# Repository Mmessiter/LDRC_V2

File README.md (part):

# LockDownRadioControl, Version 2

**A free, open-source radio control system for model aircraft. You build it yourself: a 16-channel transmitter, a receiver and a phone app.**

**Nothing to compile.** Every part takes ready-made firmware: the screen and the receiver from a web browser, the main board with a free loader. After that, everything updates itself over the air. [The short route is below](#how-to-get-one).

<p align="center"><sub>Nine of the transmitter's screens, drawn by its own code. The numbers are sample values.</sub></p>

| I want to… | Go here |
|---|---|
| See what LDRC does | [messiter.com/LDRC.html](https://messiter.com/LDRC.html) |
| Build one | [Build one](https://messiter.com/ldrc/build.html): parts, wiring, flashing, testing. [The short route](#how-to-get-one) is on this page |
| Update, or get help | [Help & updates](https://messiter.com/ldrc/help.html) |
| Set up Rotorflight from my phone | [messiter.com/rotorflight](https://messiter.com/rotorflight/) |
| Ask a question | Email Malcolm: [mmessiter@gmail.com](mailto:mmessiter@gmail.com) |

---

## What LDRC is

- **Malcolm Messiter started it in the lockdown of May 2020.** He and his club friends have flown it ever since.
- **Version 1** is in the [LockDownRadioControl](https://github.com/Mmessiter/LockDownRadioControl) repository. It still flies.
- **This repository is Version 2.** It keeps Version 1's radio link and model memories, and adds:
  - a 5-inch WiFi touchscreen on the transmitter,
  - a new receiver,
  - a free phone app for iPhone, iPad and Android.
- It flies planes, gliders and helicopters.
- It is at its best with helicopters that run [Rotorflight](https://www.rotorflight.org/), the free flight-controller software for helicopters.

## The three parts

### 1. The transmitter

<sub>A finished Version 2 transmitter (Malcolm's). The screen shows its front page.</sub>
<!-- (11 Nov 2026: Malcolm's photo of the whole white Version 2, screen lit, replaces the dim black one - his answer to question 42. One in daylight beside a helicopter is still welcome.) -->

- **The main board flies the model.** A Teensy 4.1 reads the sticks, does the mixing and runs the radio link.
- **The screen talks to the pilot.** An Elecrow 5-inch ESP32-S3 touchscreen (buy the **16 MB** one, SKU DLE06050B: the older 4 MB CrowPanel 5.0 gets fixes only) draws the pages and looks after WiFi, Bluetooth and updates.
- FrSky M9 Hall-sensor sticks, digital trims, eight three-position switches (four can be knobs), a 3D-printed case.
- **A Version 1 transmitter becomes a Version 2.** Your models, main board, sticks, switches and case back stay (fill the back's old charger hole with epoxy resin). Print the Version 2 case front from [TXV2/STL files/V2](TXV2/STL%20files/V2): it holds the new screen. Fit the screen, and update the firmware.
  <!-- (10 Nov 2026, Malcolm: "A version one back is okay, except it has an unnecessary hole for the old style charger, but it can be used if this hole is blocked up with epoxy resin".) -->
- Details: [TXV2/README.md](TXV2/README.md) and [TXV2-Screen/README.md](TXV2-Screen/README.md).

### 2. The receiver

<sub>A Version 2 receiver in a Goblin 770, beside its Nexus-X flight controller. With the short USB-C cable, the phone app does almost everything Rotorflight's Configurator does. Only flashing Rotorflight itself needs a computer.</sub>

- **A Seeed XIAO ESP32-S3 with one, two or three nRF24L01+ radios.** If one radio loses the signal, the next takes over.
- **Talks to a flight controller** over CRSF, SBUS, IBUS or PPM.
- **Sends Rotorflight telemetry** to the transmitter: battery, current, capacity used, head speed, ESC temperature.
- **Updates itself over the air**: from the phone, over WiFi, or through a Version 2 transmitter.
- **Binds to Version 1 and Version 2 transmitters.**
- **The same board has two other jobs:**
  - **dongle**: Rotorflight from your phone on a helicopter flown with any make of radio;
  - **simulator**: plugged into a computer, it lets your transmitter fly RealFlight or neXt (with no radios, it does the same for another make of receiver).
- Details: [RXV2/README.md](RXV2/README.md).

### 3. The phone app

<sub>The app's demo mode. It works without any hardware, so you can look round before you build.</sub>

- **Free** on the [App Store](https://apps.apple.com/app/id6789857533) (iPhone and iPad) and for Android from [messiter.com/apps](https://messiter.com/apps/). No adverts, no accounts, no tracking.
- **Talks to the receiver over Bluetooth.** No WiFi to join at the field.
- **Sets up Rotorflight in plain English**: wizards for a new helicopter and for tuning, PIDs, rates, governor, rescue, servos, filters, backups.
- **Reads the flight controller's black box** and suggests one filter change at a time.
- Source in [RXV2App](RXV2App).

---

## Why fly LDRC

**What gets used, and what does not.** Compare feature lists and every radio has something the others lack. What matters is which features a pilot reaches for. The ones LDRC has that most systems do not are wanted at the field all the time: a model that loads itself when you switch it on, a model or the controls handed to a friend over the air with nothing extra to buy, the whole radio updated from a button, Rotorflight set up from the transmitter. The few things other radios have that LDRC does not are rarely used by anyone, and since every line of LDRC is open they can be added the day a pilot asks: the 3-, 7- and 9-point curves were asked for one October morning and were in the transmitter by lunch.

**Range and channels: more than enough.** Some radios offer more range and more channels. Sixteen channels and about 2 km of range are more than enough for almost all model flying. [Here is why](#range-and-channels-more-than-enough).

**Every save is checked.** After a save, the transmitter and the phone app read the values back from the flight controller and compare them with what you typed. "Saved, and confirmed by reading it back" means the flight controller now holds exactly your values; a difference, or no answer, is said plainly, with the boxes that differ in red. Neither ever says "saved" on trust. Just before every write, the transmitter asks the flight controller whether it is armed; if an answer goes missing, the save is refused, never guessed. And the receiver refuses a tune that would leave roll, pitch or yaw with no response.

### Things we know of no other system doing

We checked the makers' own documents in October 2026, and read Rotorflight's three script projects for other radios again on 10 November 2026. "We know of no other" means we did not find it, not that it cannot exist.

1. **The Rotorflight tune and set-up, every bank, backed up on the transmitter and put back exactly.** Each write is read back to check it. After a restore, Rotorflight's own list of changed settings (its `diff all`) was identical to before. Ports, LED, GPS and ESC settings are not included. *Copy tuning* writes another model's PIDs, rates, governor and rescue from its backup into this one; servos, mixer, motor and switches are left alone.
2. **Change Rotorflight settings with the model switched off.** The changes are sent when the model next connects.
3. **The whole Rotorflight set-up compared with its backup, on the transmitter** (*What changed?*, 16 MB screen). Setting by setting. *Put back* returns one setting; *Undo the last save* takes back a save.
4. **Rotorflight's command line on the transmitter's screen**, and the whole set-up saved as text. (This needs the receiver's short USB cable to the flight controller.)
5. **Rotorflight set-up from an iPhone or iPad**, in plain English, with step-by-step wizards. Android too.
6. **For Rotorflight: read the black box at the field, with no computer.** See the vibration and get one filter change at a time, with undo.
7. **A chart of how long the link took to reconnect** after every drop.

<p align="center"><sub>What changed? since the backup, setting by setting. Put back returns one setting. Sample values.</sub></p>

**Rare: the right model memory loads by itself.** Switch on a model and the transmitter finds its memory. Most radios only stop you flying with the wrong one. Elsewhere we found this only on Multiplex's SMART SX, with its ID receivers (some have a fixed ID, some can be set), and on Mikado's VBar Control, which does it another way: each model's settings live in its VBar unit. Ours learns the ID of any of its own receivers.
<!-- Source: Multiplex shop, RX-5 M-LINK ID receiver: "SMART SX automatically changes the respective model memory based on the ID of the receiver" (shop.multiplex-rc.de, checked 11 Oct 2026). SMART SX 9 FLEXX M-LINK set: the RX-4/9 FLEXX M-LINK ID receiver has an adjustable ID (hobbydirekt.de/Alte-Kategorien/RC/Multiplex-RC/SMART-SX-9-FLEXX-M-LINK-Set-Multiplex-15303::270611.html, checked 11 Oct 2026). -->

<!-- TODO Malcolm: compare.md notes the Battery, Black box and Calibrate pages on the transmitter (B88) had not been tried on hardware on 10 Oct. Confirm before the site calls them proven. -->

<p align="center"><sub>Rotorflight set-up on the transmitter itself. It needs a Version 2 receiver.</sub></p>

**A new helicopter, step by step, on the transmitter** (16 MB screen). You need no laptop and no phone at the field.

- **New helicopter guide**: every Rotorflight set-up step in order. A step opens its page, and is ticked when you come back. The ticks are kept for each model.
- **Check my setup**: reads the flight controller and lists anything unfinished or odd, with a button to the page that puts it right. Red stops the model arming; amber is worth a look. It changes nothing.
- **Direction check**: tilt and turn the model, and it says whether the flight controller sees each move the right way round.
- Only putting Rotorflight itself onto the flight controller needs a computer.

<p align="center"><sub>Left: the New helicopter guide ticks off each step. Right: Check my setup says what stops the model arming. Sample values.</sub></p>

### Also on board

Other systems have most of these too.

- **Wireless buddy box** with no extra modules, and a "nudge" mode: the pupil flies, the instructor can nudge. Once it has the model, the pupil's transmitter loads it by itself. (Spektrum's Pilot Link avoids the need another way: the pupil's radio needs no model at all.)
- **Send a model memory to a friend's transmitter** over the radio link. A Version 1 transmitter can send its models to a Version 2 over the air (tested), and two Version 2s swap them.
- **One-button updates from the internet** for the whole transmitter. It can update the receiver too, and it tells you when a new version is ready.
- **Updates that protect your models**: a firmware that would read your models differently is refused, and the old one comes back by itself.
- **The link in detail**: packets a second, lost packets, longest gap, swaps between the receiver's radios, and a scan of the 2.4 GHz band for interference.
- **Six front screens, ready-made and yours to change**: an overview, head speed, the timer, the link, power, and the model with its channels. One to nine boxes each, in big digits or round dials with amber and red zones, and twelve colour themes.
- **Four banks or six** (flight modes), as Rotorflight has six. The phone app follows the transmitter's count.
- **Curves of 3, 5, 7 or 9 points** for every channel in every bank, straight, smoothed or exponential; every point keeps its height when you change the count. **Eight three-position switches**, any of them doing any job; the four on the front can be knobs.
- **Help on every page**, on the transmitter itself: 72 help pages in plain words. Most have an **animation**: a short film of the page in use, with a spoken voice. There are 76 animations; ten of them, under **Fix problems**, cure common helicopter problems.
- **See what moves what**: the Inputs and outputs page and the Switches page light the stick, trim or switch you move. *Check for duplicates* finds a model ID stored twice.
- **Spoken messages**, log files, model pictures sent from your phone, and Pong for rainy days.
- **Safety first: nothing changes in flight.** No transmitter update, file transfer or restart starts while a model is connected. A receiver update runs only with the safety on, and the receiver refuses while armed. WiFi and Bluetooth switch off whenever the model could fly. Switch a Rotorflight model on with the safety already off, and the transmitter will not connect to it until the safety is on.

<p align="center"><sub>The six ready-made front screens. Use them as they are, or change any box. Sample values.</sub></p>

<p align="center"><sub>Left: how long the link took to come back after each drop. Right: a scan of the 2.4 GHz band. Sample values.</sub></p>

### Yours to change

LDRC changes when a need appears. Its author, Malcolm Messiter, often adds a feature within a day of a pilot asking for it: the transmitter's command line and the defined front screens were each built the day they were asked for. The new version then reaches every transmitter and receiver over the internet.

It is yours to change too. Every line of code, the circuit boards and the case are open, so you can change anything yourself, or ask for it.

Commercial systems are almost always take it or leave it: you fly what the maker decided, and you cannot easily change it.

### Range and channels: more than enough

**Some radios offer more range and more channels. Sixteen channels and about 2 km of range are more than enough for almost all model flying.**

ExpressLRS is rightly praised for its range, and its claims are fair. But with a model helicopter, the radio is not what limits range. Your eyesight is.

In Malcolm's own tests at ground level, LDRC Version 2 kept its link at more than a kilometre. The makers of its radio modules claim more than two. Nobody can see a helicopter well enough to fly it at a kilometre, so more range than that makes no difference in the air.

Channels are the same story. A helicopter with a flight controller uses about eight, and most aeroplanes fewer. Sixteen leaves room to spare.

What matters more is that the link never fails. Now and then a commercial radio fails and a model crashes, through a faulty part or faulty assembly. Commercial makers must make a profit, so they have every reason to build quickly and with economical parts. LDRC is not built for profit. In about six years of flying, it has never had a radio failure, nor any problem with range.

### Side by side

Key: **Yes** · **Partly** · **No** · **Not found** = not in the maker's documents we read · **?** = not checked, or we could not confirm · **n/a** = does not apply.
Prices are approximate retail prices in October 2026. LDRC prices are for parts only.

**Link and hardware**

| | LDRC V2 | EdgeTX + ExpressLRS | FrSky Ethos | Spektrum | Mikado VBar Control |
|---|---|---|---|---|---|
| Open-source firmware | **Yes** | **Yes** | No | No | No |
| Boards and case you can build yourself | **Yes** | Partly: ExpressLRS publishes DIY receiver and module boards; the radio is bought | No | No | No |
| Channels | 16 (a helicopter with a flight controller uses about eight) | Up to 32 (ExpressLRS carries 16) | Up to 24 | 20 | ? |
| Fastest packet rate | 500 a second | Up to 1,000 a second | ? | ? | ? |
| Bands | 2.4 GHz | 2.4 GHz and 900 MHz | 2.4 GHz and 900 MHz | 2.4 GHz | 2.4 GHz |
| Range | More than 1 km in ground-level tests (the module makers claim more than 2 km): more than enough for almost all model flying | "Over 40 km" (ExpressLRS's own figure, ideal conditions) | "50–100 km" (FrSky's claim) | ? | ? |
| Servo (PWM) outputs on the receiver | Version 1 receiver only | **Yes** | **Yes** | **Yes** | The VBar unit drives the servos |
| GPS and vario | Version 1 receiver only | **Yes** | **Yes** | **Yes** | Partly |
| CE-marked radio modules | **Yes** (Ebyte E01, FCC ID 2ALPH-E01) | **Yes** | **Yes** | **Yes** | **Yes** |
| Price, about | Transmitter: the parts priced so far come to £120–£143, before the switches, trims, radio module, battery, circuit board, case and small parts. Receiver about £35. Parts only, approximate | Radio about £130–£200 (Jumper T15 to TX16S MKII); ExpressLRS receivers from about £11 to £19 (HappyModel EP2, RadioMaster RP1), ready to fly | £460–£600 (X20 family) | £430 (NX10+) | £750 (radio + VBar EVO flybarless unit and receiver) |

**The transmitter**

| | LDRC V2 | EdgeTX + ExpressLRS | FrSky Ethos | Spektrum | Mikado VBar Control |
|---|---|---|---|---|---|
| Loads the right model memory by itself | **Yes**, rare (elsewhere found only on Multiplex SMART SX and VBar Control) | No: Model Match only blocks control | Not found | No: ModelMatch only blocks the wrong memory | **Yes**, another way: each model's settings live in its VBar unit |
| Wireless buddy box, no extra hardware | **Yes**, with nudge; the pupil's radio loads the same model | Partly: radios with Bluetooth | **Yes** | **Yes** | **Yes** |
| Send a model memory to another transmitter, no wires | **Yes**, over the radio link | No | ? | **Yes** (iX20, Bluetooth) | Partly |
| Updates itself from the internet | **Yes**, the whole radio, with automatic roll-back | No: a computer and a browser | No: USB or SD card | **Yes**, WiFi | **Yes**, WiFi |
| Updates the receiver through the transmitter | **Yes** | Partly: the receiver's own WiFi page | **Yes** | ? | **Yes** |
| Help on every page, on the radio | **Yes**: 72 help pages and 76 spoken animations | Not found: online manual | ? | ? | **Yes**: a (?) on every setting |
| Scripts and add-on apps | No, by choice | **Yes**: Lua | **Yes**: Lua | **Yes**: apps on iX20 | **Yes**: app store |
| Mixer depth | 16 channels, 4 or 6 flight modes, 32 mixes | Much deeper | Deep | Deep | Made for helicopters |
| Curve points per channel | 3, 5, 7 or 9, every point remembered | Up to 17 | ? | ? | ? |
| Any switch, any job | **Yes**: 8 three-position switches, the front four can be knobs | **Yes** | **Yes** | **Yes** | **Yes** |

**Helicopters with Rotorflight**

| | LDRC V2 | EdgeTX + ExpressLRS | FrSky Ethos | Spektrum | Mikado VBar Control |
|---|---|---|---|---|---|
| Rotorflight telemetry on the transmitter | **Yes** | **Yes** | **Yes** | Partly | **Yes**, for VBar units |
| Rotorflight set-up from the transmitter | **Yes**: Easy tuning, PIDs, rates, governor, rescue, servos, travel extents, filters, switches and knobs, copy a bank, battery, black box, first-time basics. On the 16 MB screen: a new-helicopter guide, a set-up check and a direction check | **Yes**: PIDs, rates, governor, rescue, servos, mixer, filters, battery, ESCs of 8 makes (Rotorflight's Lua scripts). A newer suite, in pre-release snapshots, adds a set-up wizard | **Yes, and wider**: over 100 pages, a set-up wizard, ESC tools | Not found | **Yes**, for VBar units |
| Back up Rotorflight on the transmitter, restore exactly | **Yes**: every bank; not ports, LED, GPS or ESC | Not in the Rotorflight scripts | No | n/a | A separate app, for VBar |
| Edit with the model switched off, send later | **Yes** | Not found | Not found | n/a | Not found |
| Compare Rotorflight with its backup, put one setting back, undo a save | **Yes** (16 MB screen) | Not found. Rotorflight's newer suite, in a preview, tracks what an in-flight tuning session changed, and can put it back | Not found | n/a | n/a |
| Phone app for Rotorflight on iPhone and Android | **Yes**, free | Partly: Rotorflight's configurator on Android (app, or Chrome at cfg.rotorflight.org), by USB cable; no iPhone app | as EdgeTX | n/a (an app for its own flybarless units) | n/a (set-up is on the radio) |
| Black box vibration check without a computer | **Yes** | No | Partly: no spectrum | No | **Yes**, for VBar |
| ESC programming | Partly: from the phone, Scorpion only, beta | **Yes**: 8 makes (Rotorflight's Lua scripts) | **Yes**: 10 ESC families | Spektrum Smart ESCs | **Yes** |

<details>
<summary>Sources for the table</summary>

- ExpressLRS: [home page](https://www.expresslrs.org/), [signal health and range](https://www.expresslrs.org/info/signal-health/), [Model Match](https://www.expresslrs.org/software/model-config-match/), [WiFi updating](https://www.expresslrs.org/software/updating/wifi-updating/), [DIY receivers](https://www.expresslrs.org/hardware/special-targets/diy-rx/)
- EdgeTX: [limits in the source](https://github.com/EdgeTX/edgetx/blob/main/radio/src/dataconstants.h), [Bluetooth](https://manual.edgetx.org/v2.9/edgetx-how-to/use-bluetooth-with-edgetx), [updating with EdgeTX Buddy](https://manual.edgetx.org/installing-and-updating-edgetx/update-from-opentx-to-edgetx)
- Rotorflight: [Lua scripts](https://github.com/rotorflight/rotorflight-lua-scripts) ([their pages in release 2.3.0](https://github.com/rotorflight/rotorflight-lua-scripts/tree/release/2.3.0/src/SCRIPTS/RF2/PAGES)), [Ethos suite](https://github.com/rotorflight/rotorflight-lua-ethos-suite), [newer suite for EdgeTX](https://github.com/rotorflight/rotorflight-lua-edgetx-suite) (snapshot 0.2.1; all three read again on 10 November 2026), [configurator releases](https://github.com/rotorflight/rotorflight-configurator/releases)
- FrSky: [Tandem X20 review](https://oscarliang.com/frsky-tandem-x20), [ACCESS receivers](https://oscarliang.com/frsky-access-protocol/)
- Spektrum: [NX10+](https://modelhelicopters.co.uk/products/spektrum-nx10-20-channel-dsmx-transmitter-only-spmr10120eu), [iX20](https://modelhelicopters.co.uk/products/spektrum-ix20-20-channel-smart-transmitter-spmr20100eu-spmr20100eu), [wireless trainer](https://cdn.shopify.com/s/files/1/0024/8617/3749/files/SPMR6775-Manual-EN.pdf) (the NX6 manual, page 22)
- Mikado: [VBar Control Touch EVO](https://modelhelicopters.co.uk/products/mikado-vcontrol-touch-evo-combo-red-05585), [release notes, Nov 2025](https://www.vstabi.info/en/update_release_nov_2025), [VBar Control Touch manual](https://www.mikado-heli.de/downloads/anleitungen/vcontrol/VBar_Control_Touch_201_EN.pdf) (help on the radio; the model's screen on connection), [Model Aviation review, August 2019](https://www.modelaviation.com/mikado-vbar-control) (each model's settings live in its VBar unit)
- Multiplex: [RX-5 M-LINK ID1 receiver](https://shop.multiplex-rc.de/en/receiver-rx-5-m-link-id-1-2-4-ghz-p5007/) (SMART SX loads the model memory from the receiver's ID)
- LDRC's own facts come from the code and help texts in this repository.

</details>

### The price, honestly

- The transmitter parts priced so far come to £120–£143, before the switches, trims, radio module, battery, circuit board, case and small parts. A budget EdgeTX radio is about £130.
- It costs far less than the X20, NX10+ or VBar Control in the table. Ethos and Spektrum also make cheaper radios (a FrSky X14 is about £170).
- The value is not "the cheapest radio". Budget EdgeTX radios can already tune Rotorflight with Rotorflight's own scripts. We did not find the Rotorflight backup, editing with the model off, the comparison with the backup, or the command line on any other radio.
<!-- Sources: FrSky Twin X14 £168–£178.90 at FlyingTech UK; VBar Control Touch EVO combo £749.99 "Includes VBar EVO VLink Flybarless/Receiver unit" (modelhelicopters.co.uk), both checked 11 Oct 2026. TODO Malcolm: once the full parts total is known, put back a fair comparison with a budget EdgeTX radio. -->
- Add your own time: a transmitter takes a day, but an intense one (Malcolm advises at least two); a receiver under an hour; a dongle about ten minutes.

<!-- TODO Malcolm: the transmitter says "over £120 in parts (approximate)", as on the website: the parts the Build one page prices (Teensy, INA219, Pololu 2808, CrowPanel, gimbals £40-£60 a pair) already come to about £120-£143, and the rest are unpriced. "about £35 of parts" for the receiver is the receiver's own help text (RXV2/data/dongle.html), the same as the website. Please re-cost the V2 parts. -->

---

## The numbers

- **16 channels**, about 2,000 steps each (whole microseconds, 500 to 2,500), sent in 12-bit slots; 11-bit out of the receiver on CRSF or SBUS.
- **500 packets a second.** Fewer while buddy-boxing, because the instructor's transmitter also talks to the pupil's.
- **Frequency hopping across 83 channels** of the 2.4 GHz band, about 100 hops a second. The receiver chooses each next channel.
- **250 kbit/s** over the air. One quick retry for a lost packet, then fresh stick data, never a stale backlog.
- **1, 2 or 3 radios** in a receiver, with automatic switching.
- **Outputs:** CRSF (250 frames a second by default), SBUS, IBUS, PPM.
- **Measured on the first Version 2 flight** (Goblin RAW 420, 5 October 2026): 491 packets a second on average, 0.21 % of packets lost, longest gap 15 ms.
- **Range:** more than 1 km in ground-level tests. The radio modules' makers claim more than 2 km.
- **90 model memories**, backups as many as the card holds, 4 or 6 banks (flight modes) per model, 32 mixes, 3 rates, 8 macros, help on every page (72 help pages, 76 spoken animations).

<!-- TODO Malcolm: 90 memories: the code (MAXMODELNUMBER 91: the Models page, automatic model selection and the buddy match run 1-90) and MODELS.TXT say 90. Only the Check IDs page (Model_IDs.h) scans 1-89: please check memory 90 shows there. -->

---

## How to get one

There is nothing to buy from us. You build your own, and Malcolm will help.

**Nothing to compile.** Every part takes ready-made firmware, once, by USB:

| Part | Its firmware | What you need |
|---|---|---|
| The screen | [Flash it from your browser](https://messiter.com/ldrc/flash-screen.html) | Chrome or Edge on a computer, a USB-C data cable |
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
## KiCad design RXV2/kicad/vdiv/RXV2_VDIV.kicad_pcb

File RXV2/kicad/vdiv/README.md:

# The battery divider board (RXV2_VDIV v1.2)

A tiny board that lets the receiver read the **flight battery's voltage** itself, for a flight controller that does not
send it over CRSF telemetry. About 22 × 12 mm, two layers, 1.6 mm. Up to **12S**.

<sub>Drawn from its design files. The printing on the back says how to wire it.</sub>

## The files

| File | What it is |
|---|---|
| `RXV2_VDIV_v1.2_gerbers.zip` | **Send this to a PCB maker**: two layers, 1.6 mm |
| `RXV2_VDIV_schematic.pdf` | The circuit, to read without KiCad |
| `RXV2_VDIV.kicad_pro`, `.kicad_sch`, `.kicad_pcb`, `RXV2_VDIV.pretty`, `fp-lib-table` | The design, for KiCad |

KiCad's design check finds no errors and nothing unconnected.

## How it works

The flight battery's + goes through 220 kΩ (two 110 kΩ) and 10 kΩ to ground: a ratio of **23 to 1**, so a full 12S
pack (50.4 V) gives the receiver about 2.2 V. A 1 kΩ resistor, a 3.6 V zener and a 100 nF capacitor protect the
receiver's pad.

## Wiring it

- Its three pins: **1 = SENSE** (to the receiver's pad **D9**), **2 = BAT+** (the flight battery's +), **3 = GND**.
  The back of the board says the same. It is made so that a plug the wrong way round does no harm.
- **Only with one or two radios:** D9 is radio 3's pad.
- Then, in the app: **Receiver settings > Receiver battery**: Pin D9, Ratio 23.0, then **Save battery settings**.

Check the voltage it reports against a meter before you trust it.

Licence: boards CERN-OHL-S-2.0. See [../../../LICENSING.md](../../../LICENSING.md).

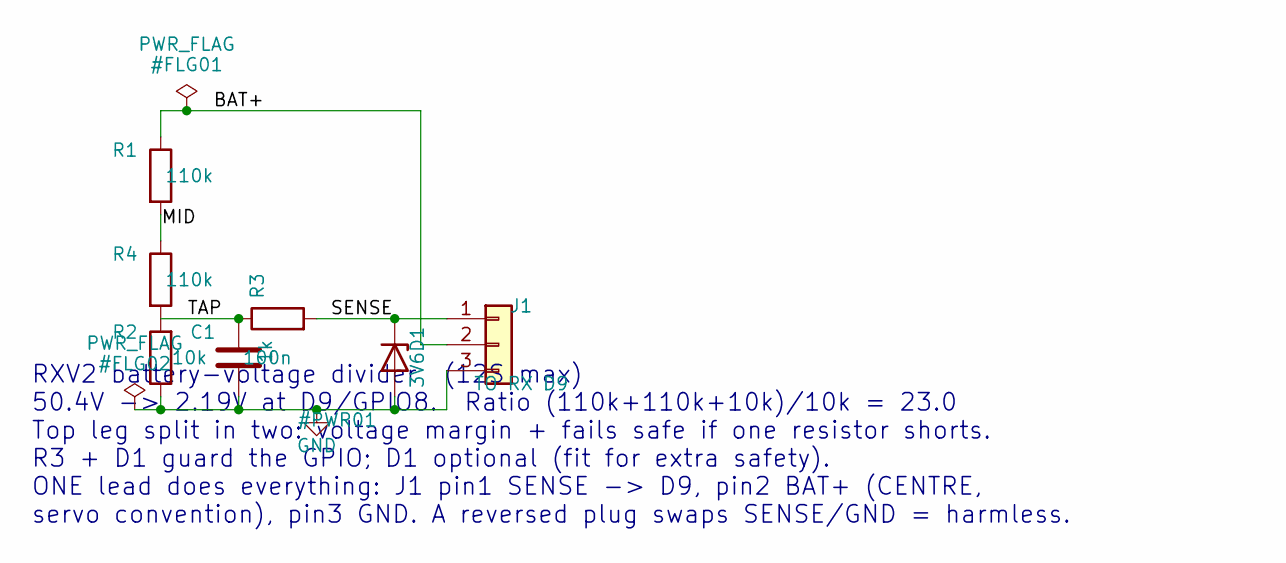
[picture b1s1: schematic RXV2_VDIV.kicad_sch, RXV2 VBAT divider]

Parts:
C1: 100n; C_0805_2012Metric
D1: 3V6; D_SOD-323
J1: TO RX D9; PinHeader_1x03_P2.54mm_Vertical
R1, R4: 110k; R_1206_3216Metric
R2: 10k; R_1206_3216Metric
R3: 1k; R_1206_3216Metric

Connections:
/BAT+: J1.2, R1.1
/MID: R1.2, R4.1
/SENSE: D1.1 (K), J1.1, R3.2
/TAP: C1.2, R2.2, R3.1, R4.2
GND: C1.1, D1.2 (A), J1.3, R2.1

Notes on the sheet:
RXV2 battery-voltage divider (12S max) 50.4V -> 2.19V at D9/GPIO8. Ratio (110k+110k+10k)/10k = 23.0 Top leg split in two: voltage margin + fails safe if one resistor shorts. R3 + D1 guard the GPIO; D1 optional (fit for extra safety). ONE lead does everything: J1 pin1 SENSE -> D9, pin2 BAT+ (CENTRE,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

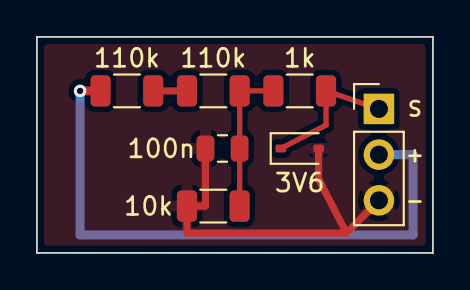
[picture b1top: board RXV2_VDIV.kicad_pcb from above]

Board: 2 copper layers, 22.0 x 12.0 mm, 7 parts (0 on the bottom side), 5 nets.

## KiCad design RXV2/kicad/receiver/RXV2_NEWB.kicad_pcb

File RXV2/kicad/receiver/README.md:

# The receiver's circuit board (RXV2_NEWB)

The production board of the Version 2 receiver: a Seeed **XIAO ESP32-S3** and two Ebyte **E01-ML01SP4** radios, one on
each side. About 46 × 22 mm, two layers, 1.6 mm.

<sub>Malcolm's receiver, both sides, in clear heat-shrink. Left: the regulator side. Right: the XIAO side.</sub>

## The files

| File | What it is |
|---|---|
| `RXV2_NEWB_gerbers.zip` | **Send this to a PCB maker**: two layers, 1.6 mm |
| `RXV2_NEWB_schematic.pdf` | The circuit, to read without KiCad |
| `RXV2_NEWB.kicad_pro`, `.kicad_sch`, `.kicad_pcb` | The design, for KiCad 10 |

The Gerbers were plotted from this board file with its own settings on 10 November 2026. KiCad's design check finds
no errors and nothing unconnected. The 3D models of the Pololu regulator and the XIAO are not included: KiCad draws
the board without them.

## Fitting the parts

The parts list is in [../../README.md](../../README.md#on-the-circuit-board), with the advice on soldering the XIAO.

1. **The AMS1117 (U3) first.** It sits under the XIAO, so it must go on before the XIAO does.
2. **The surface-mount parts:** the capacitors, the status LED and its 100 Ω resistor, and the two radios.
   **The LED:** its − (cathode) goes to the pad joined to the ground plane; you can see which on the board.
   The wrong way round, it simply does not light.
3. **The Pololu S7V7F5 regulator (U4): fit it as in the photo**, flat on the board with its component side towards
   the board and its flat, printed side (VIN, GND, VOUT) facing out. (The schematic draws a 7805-style regulator; the
   photo is the guide.)
4. **The lead socket** (J2, JST-GH 4-pin).
5. **The XIAO last.** Finish every one of its pins with the iron (see the parts list's advice).

Check the lead to the flight controller with a meter before the first power-up.

Licence: boards CERN-OHL-S-2.0. See [../../../LICENSING.md](../../../LICENSING.md).

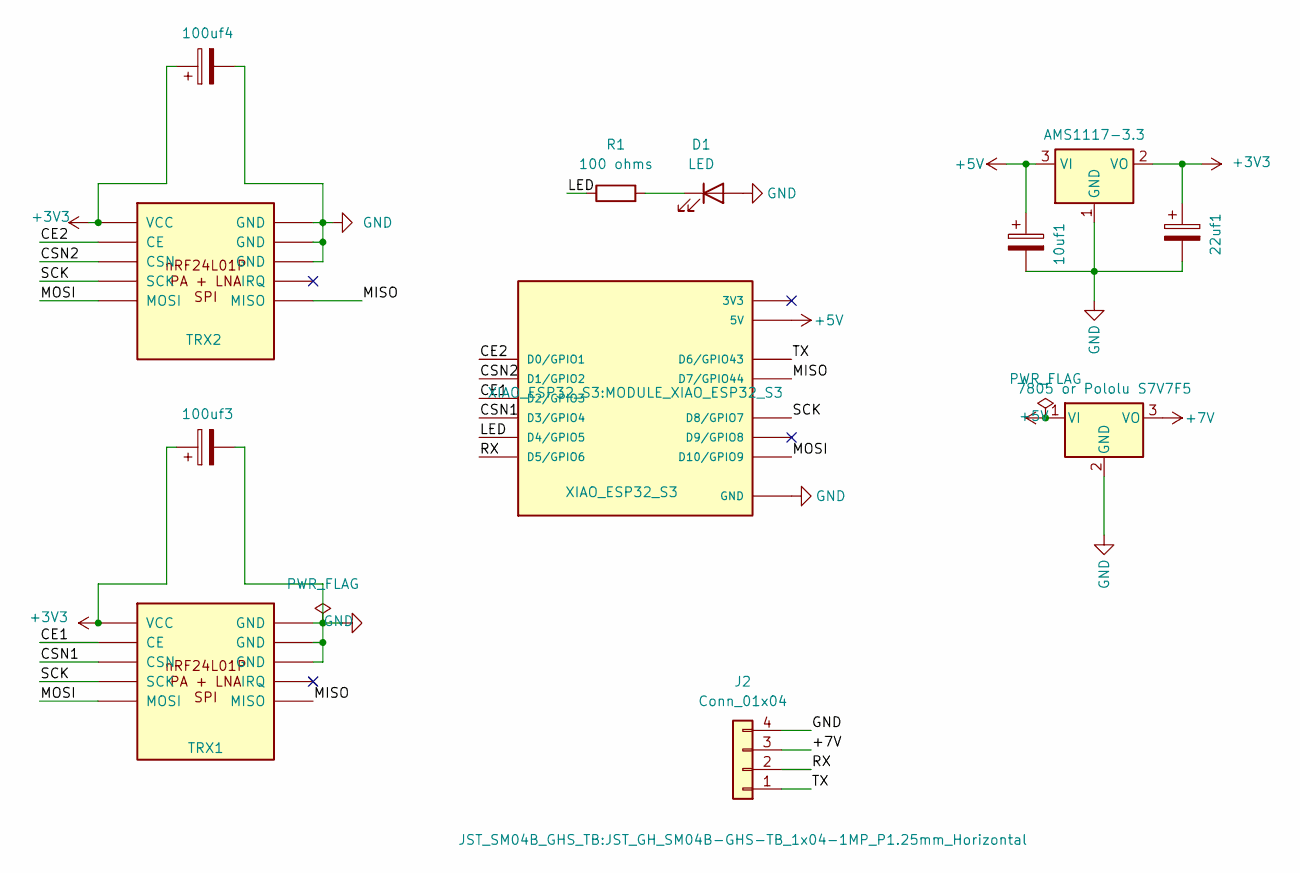
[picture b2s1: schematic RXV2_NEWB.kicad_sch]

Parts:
10uf1, 22uf1, 100uf3, 100uf4: C_Polarized; C_1206_3216Metric
D1: LED; LED_1206_3216Metric_Pad1.42x1.75mm_HandSolder
J2: Conn_01x04; JST_GH_SM04B-GHS-TB_1x04-1MP_P1.25mm_Horizontal
R1: 100 ohms; R_1206_3216Metric_Pad1.30x1.75mm_HandSolder
TRX1, TRX2: EBYTE_E01-ML01SP4_14.5x18mm_SMD
U2: XIAO_ESP32_S3; MODULE_XIAO_ESP32_S3; PARTREV April 22nd, 2026
U3: AMS1117-3.3; SOT-223-3_TabPin2
U4: 7805 or Pololu S7V7F5; TO-220-3_Vertical

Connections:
+3V3: 22uf1.1, 100uf3.1, 100uf4.1, TRX1.1 (VCC), TRX2.1 (VCC), U3.2 (VO); also elsewhere on the board
+5V: 10uf1.1, U2.14 (5V), U3.3 (VI), U4.1 (VI)
+7V: J2.3, U4.3 (VO)
/CE1: TRX1.2 (CE), U2.3 (D2/GPIO3)
/CE2: TRX2.2 (CE), U2.1 (D0/GPIO1)
/CSN1: TRX1.3 (CSN), U2.4 (D3/GPIO4)
/CSN2: TRX2.3 (CSN), U2.2 (D1/GPIO2)
/LED: R1.1, U2.5 (D4/GPIO5)
/MISO: TRX1.6 (MISO), TRX2.6 (MISO), U2.8 (D7/GPIO44)
/MOSI: TRX1.5 (MOSI), TRX2.5 (MOSI), U2.11 (D10/GPIO9)
/RX: J2.2, U2.6 (D5/GPIO6)
/SCK: TRX1.4 (SCK), TRX2.4 (SCK), U2.9 (D8/GPIO7)
/TX: J2.1, U2.7 (D6/GPIO43)
GND: 10uf1.2, 22uf1.2, 100uf3.2, 100uf4.2, D1.2 (A), J2.4, TRX1.8 (GND), TRX1.9 (GND), TRX1.10 (GND), TRX2.8 (GND), TRX2.9 (GND), TRX2.10 (GND), U2.13 (GND), U3.1 (GND), U4.2 (GND); also elsewhere on the board
unnamed: D1.1 (K), R1.2

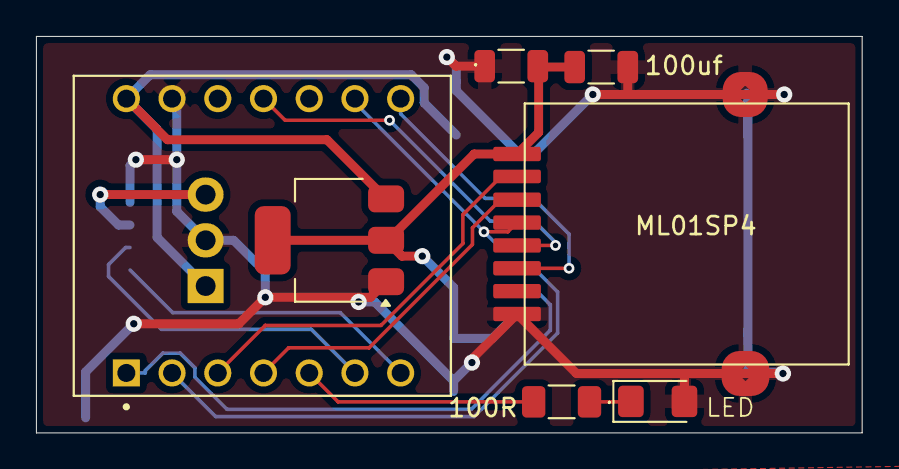
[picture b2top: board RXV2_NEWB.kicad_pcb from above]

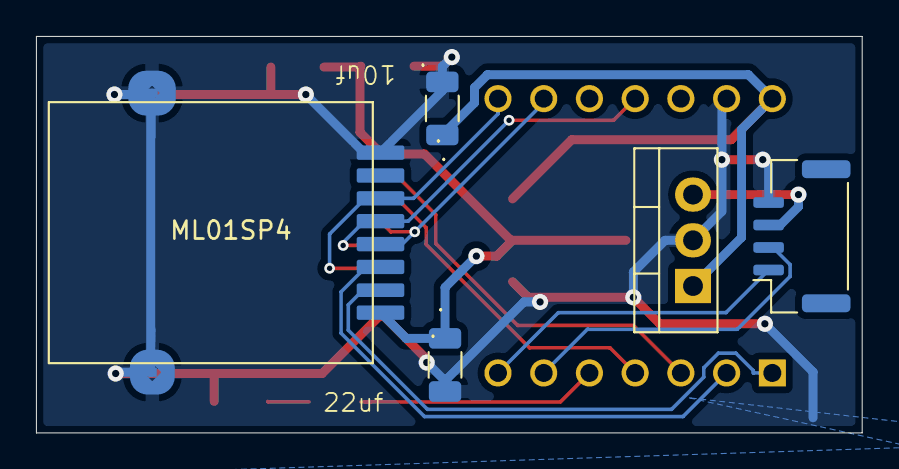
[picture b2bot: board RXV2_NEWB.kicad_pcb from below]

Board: 2 copper layers, 45.9 x 22.0 mm, 12 parts (5 on the bottom side), 15 nets.

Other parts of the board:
100uf: C_Polarized; C_1206_3216Metric

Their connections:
+3V3: 100uf.1; also elsewhere on the board
GND: 100uf.2; also elsewhere on the board

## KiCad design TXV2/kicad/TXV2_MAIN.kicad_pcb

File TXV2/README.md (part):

# The Version 2 transmitter

<sub>A finished Version 2 transmitter (Malcolm's). The screen shows its front page.</sub>

**A 16-channel 2.4 GHz transmitter that you build yourself.**

- **The main board flies the model.** A Teensy 4.1 reads the sticks, does the mixing and runs the radio link.
- **The screen talks to the pilot.** Elecrow's 5-inch IPS panel (ESP32-S3 with 16 MB, touchscreen, WiFi, Bluetooth) draws the pages and fetches updates. Its firmware is in [../TXV2-Screen](../TXV2-Screen).
- **It is Version 1 with a new screen and a new case front.** The main board, radio, sticks and switches are Version 1's.
- **Have a Version 1?** Your models, main board, sticks, switches and case back stay (fill the back's old charger hole with epoxy resin). Print the Version 2 case front from [STL files/V2](STL%20files/V2): it holds the new screen. Fit the screen, and update the firmware. Keep your Teensy's own card (copy it to a computer first). Do not make the example card.
  <!-- (10 Nov 2026, Malcolm: "A version one back is okay, except it has an unnecessary hole for the old style charger, but it can be used if this hole is blocked up with epoxy resin".) -->
- **Building one?** Start with [Build one](https://messiter.com/ldrc/build.html) on the website. This README has the same steps, with the files. **Nothing to compile:** the Teensy takes a ready-made file, and the screen is flashed from a web browser.

---

## What it does

<sub>One front screen in six of the twelve themes. Sample values.</sub>

**Flying**
- 16 channels. Any stick, switch or knob can drive any channel.
- 4 banks (flight modes), or 6 with **Six banks** on (Model options), each with its own curves, trims and mixes. With a Version 2 receiver, the phone app follows the transmitter's count.
- Curves of 3, 5, 7 or 9 points for every channel in every bank (every point keeps its height when you change the count), 3 rates, 32 mixes, 8 timed macros, servo speed, subtrim, reverse, failsafe.
- **Eight switches, any job:** banks, motor, safety, rates, buddy, or the input of any channel 5–16.
- **Wireless buddy box** with no extra hardware, and a "nudge" mode for the instructor.

**Model memories**
- 90 model memories, and as many backups as the card holds.
  <!-- TODO Malcolm: 90 memories: the code (MAXMODELNUMBER 91: the Models page, automatic model selection and the buddy match run 1-90) and MODELS.TXT say 90. Only the Check IDs page (Model_IDs.h) scans 1-89: please check memory 90 shows there. -->
- **The right memory loads by itself** when you switch a model on. This is rare: elsewhere we found it only on Multiplex's SMART SX, with its ID receivers (some have a fixed ID, some can be set), and on Mikado's VBar Control, which keeps each model's settings in the model.
- **Check for duplicates** lists every model with its stored ID, and names any two that share one.
- **Send a model memory to another transmitter** over the radio link. A Version 1 transmitter can send its models to a Version 2 over the air (tested), and two Version 2s swap them.

**The screen**
- **Six front screens, ready-made and yours to change:** an overview, head speed, the timer, the link, power, and the model with its channels. One to nine boxes each, in big numbers or round dials, with amber and red zones.
- **Twelve colour themes**, each one editable. Give each box its own theme, or press **Apply to all boxes** to give the whole screen one.
- **Model pictures** sent from your phone by scanning a QR code.
- **See what moves what:** the Inputs and outputs page and the Switches page light the stick, trim or switch you move.
- **Help on every page:** 72 help pages in plain words. Most have an **animation** of the page in use, with a spoken voice. There are 76 animations; ten of them, under **Fix problems**, cure common helicopter problems.
- Spoken messages, log files, and Pong for rainy days.

<sub>The six ready-made front screens. Use them as they are, or change any box. Sample values.</sub>

<sub>Left: a front screen of round dials, each with its amber and red zones. Right: give a box its own theme, or apply it to all boxes. Sample values.</sub>

**Rotorflight on the transmitter** (needs a Version 2 receiver)
- Easy tuning, PIDs, rates, governor, rescue, servos, travel extents, filters, switches and knobs, copy a bank, battery, black box, calibrate, first-time basics. On the 16 MB screen, the beeper and Rotorflight's name for the model too.
- **A new helicopter, step by step** (16 MB screen). The **New helicopter guide** takes you through every set-up step in order and ticks each one off. **Check my setup** lists anything unfinished and says what stops the model arming. **Direction check** tells you whether the flight controller is the right way round.
- **Back up the Rotorflight tune and set-up**, every bank, to the card, and put it back exactly. Ports, LED, GPS and ESC settings are not included. **Copy tuning** writes another model's PIDs, rates, governor and rescue from its backup into this one.
- **What changed?** (16 MB screen) compares the whole set-up with its backup, setting by setting, and puts any one setting back. **Undo the last save** takes back a save. We did not find this comparison on any other radio.
- **Edit with the model switched off.** The changes go across when it next connects.
- **Every save is read back** from the flight controller and compared with what you typed, before the page says saved. A difference, or no answer, is told.
- With the receiver's USB cable to the flight controller: setting up the selectors and knobs on Switches and knobs (they then work without the cable), Rotorflight's command line, and the whole set-up saved to the card as text (Rotorflight's `diff all`).
- The settings travel over Bluetooth from the screen to the receiver, never over the flying link, and only while the model is disarmed.

<sub>Left: Guide &amp; checks, five helpers and the command line. Right: Direction check, as you tilt the model. Sample values.</sub>

<!-- TODO Malcolm: compare.md says Battery, Black box and Calibrate (B88) were not yet tried on hardware on 10 Oct. Confirm before release notes call them proven. -->

**Link and diagnostics**
- Packets a second, lost packets, longest gap, swaps between the receiver's radios.
- A chart of reconnection times, and a scan of the 2.4 GHz band for interference.

**Updates and safety**
- **One button updates the whole transmitter** from the internet: screen, card, main board, help texts. It tells you when a new version is ready.
- **The receiver can be updated through the transmitter.**
- Nothing changes in flight. No transmitter update, file transfer or restart starts while a model is connected. A receiver update runs only with the safety on, and the receiver refuses while armed. WiFi and Bluetooth switch off whenever the model could fly.
- Switch a Rotorflight model on with the safety already off, and the transmitter will not connect to it until the safety is on.

<sub>Rotorflight set-up on the transmitter. Sample values.</sub>

---

**What gets used.** Compare feature lists and every radio has something the others lack. What matters is which features a pilot reaches for. The ones above that most systems do not have - a model that loads itself, a model or the controls handed over the air with nothing extra to buy, the whole radio updated from a button, Rotorflight set up from the transmitter - are wanted at the field all the time. The few things other radios have that this one does not are rarely used by anyone, and since every line is open they can be added the day a pilot asks: the 3-, 7- and 9-point curves were asked for one October morning and were in the transmitter by lunch.

## What is in this folder

| | |
|---|---|
| `TransmitterCode/` | The Teensy 4.1 firmware (PlatformIO). `include/` holds nearly all of it, one header per subject. `src/main.cpp` is set-up and the main loop |
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
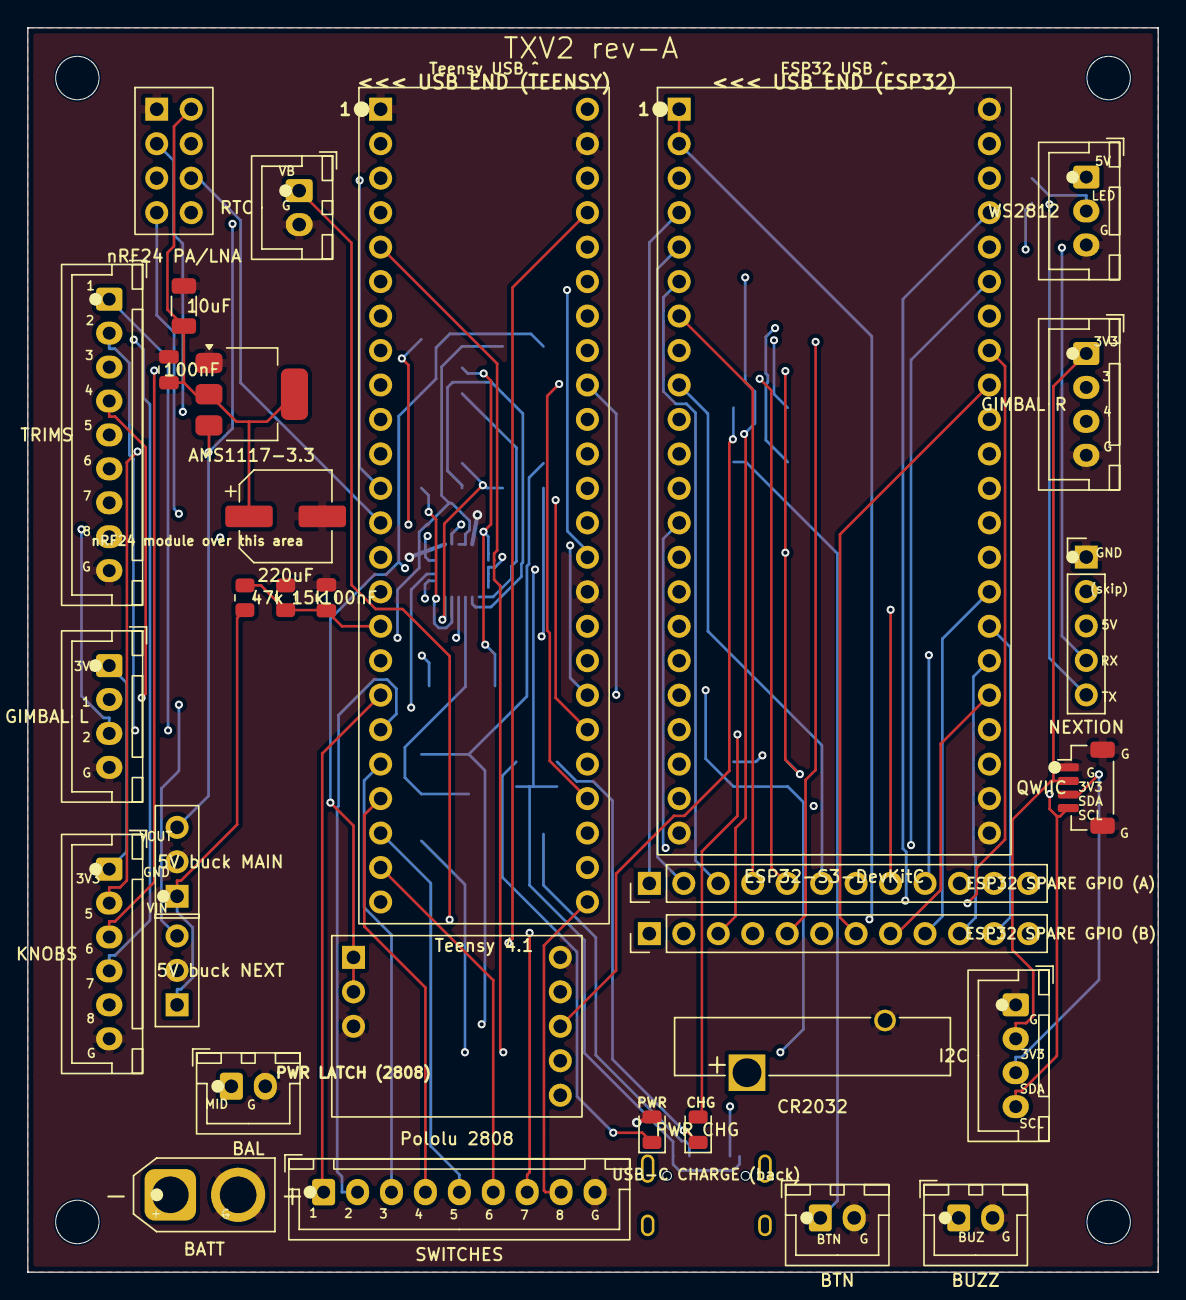
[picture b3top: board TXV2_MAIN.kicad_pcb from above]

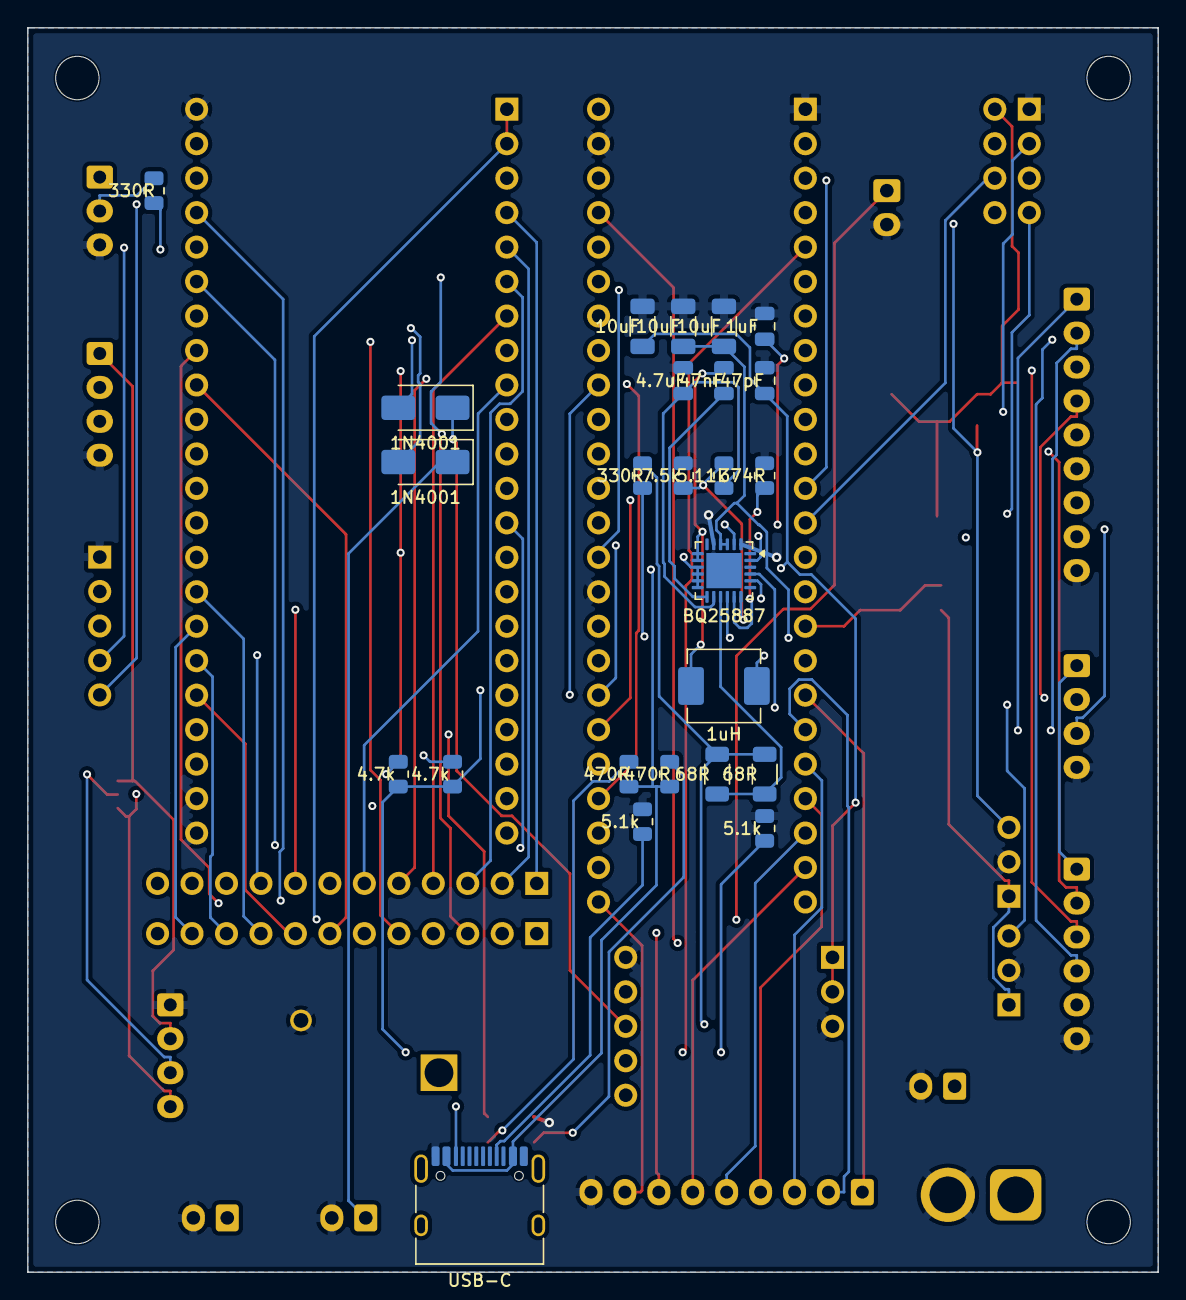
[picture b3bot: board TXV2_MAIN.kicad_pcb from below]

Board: 4 copper layers, 83.3 x 91.7 mm, 61 parts (25 on the bottom side), 92 nets.

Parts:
BT1: CR2032; Battery_Panasonic_CR2032-VS1N_Vertical_CircularHoles
C1: 1uF; C_0805_2012Metric
C2, C3, C4, C9: 10uF; C_1206_3216Metric
C5: 47pF; C_0805_2012Metric
C6: 47nF; C_0805_2012Metric
C7: 4.7uF; C_0805_2012Metric
C8: 220uF; CP_Elec_6.3x7.7
C10, C11: 100nF; C_0805_2012Metric
D1: PWR; LED_0805_2012Metric
D2: CHG; LED_0805_2012Metric
D3, D4: 1N4001; D_SMA
H1, H2, H3, H4: M3; MountingHole_3.2mm_M3
J1: USB-C; USB_C_Receptacle_HRO_TYPE-C-31-M-12
J2: NEXTION; PinHeader_1x05_P2.54mm_Vertical
J3: BATT; AMASS_XT30U-F_1x02_P5.0mm_Vertical
J4: BAL; JST_XH_B2B-XH-A_1x02_P2.50mm_Vertical
J5: BTN; JST_XH_B2B-XH-A_1x02_P2.50mm_Vertical
J6: GIMBAL L; JST_XH_B4B-XH-A_1x04_P2.50mm_Vertical
J7: GIMBAL R; JST_XH_B4B-XH-A_1x04_P2.50mm_Vertical
J8: KNOBS; JST_XH_B6B-XH-A_1x06_P2.50mm_Vertical
J9: SWITCHES; JST_XH_B9B-XH-A_1x09_P2.50mm_Vertical
J10: TRIMS; JST_XH_B9B-XH-A_1x09_P2.50mm_Vertical
J11: WS2812; JST_XH_B3B-XH-A_1x03_P2.50mm_Vertical
J12: QWIIC; JST_SH_BM04B-SRSS-TB_1x04-1MP_P1.00mm_Vertical
J13: I2C; JST_XH_B4B-XH-A_1x04_P2.50mm_Vertical
J14: RTC; JST_XH_B2B-XH-A_1x02_P2.50mm_Vertical
J15: ESP32 SPARE GPIO (A); PinHeader_1x12_P2.54mm_Vertical
J16: ESP32 SPARE GPIO (B); PinHeader_1x12_P2.54mm_Vertical
J17: BUZZ; JST_XH_B2B-XH-A_1x02_P2.50mm_Vertical
L1: 1uH; L_Vishay_IHLP-2020
R1, R14: 330R; R_0805_2012Metric
R2, R3: 68R; R_1206_3216Metric
R4: 5.11k; R_0805_2012Metric
R5: 7.5k; R_0805_2012Metric
R6: 374R; R_0805_2012Metric
R7, R8: 5.1k; R_0805_2012Metric
R9, R10: 470R; R_0805_2012Metric
R12, R13: 4.7k; R_0805_2012Metric
R15: 47k; R_0805_2012Metric
R16: 15k; R_0805_2012Metric
U1: Teensy 4.1; Teensy41_Socket
U2: ESP32-S3-DevKitC; DevKitC1_Socket
U3: nRF24 PA/LNA; NRF24_Socket_2x4
U4: Pololu 2808; Pololu2808_Socket
U5: 5V buck MAIN; Buck3pin_VGV
U7: BQ25887; HVQFN-24-1EP_4x4mm_P0.5mm_EP2.6x2.6mm
U8: AMS1117-3.3; SOT-223-3_TabPin2
U9: 5V buck NEXT; Buck3pin_VGV

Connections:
+3V3_RF: C8.1, C9.1, C10.1, U3.2, U8.2
+3V3_T: J6.1, J7.1, J8.1, J12.2, J13.2, R12.1, R13.1, U1.15, U1.27
+5V: J11.1, U1.25, U2.21, U5.3, U8.3
+5V_NEXT: J2.3, U9.3
BTN_SENSE: D3.2, U1.6
BTST: C6.1, U7.12
BUZZER: J17.1, U1.5
CB_PATH: R2.1, R3.1, U7.10
CELL_MID: J4.1, R1.2, R2.2, R3.2
CHG_ILIM: R6.1, U7.8
CHG_STAT: D2.2, U7.2
CHG_TS: R4.2, R5.1, U7.7
ESP_3V3: J16.12, U2.1, U2.2
ESP_G1: J16.2, U2.26
ESP_G2: J16.3, U2.27
ESP_G3: J15.7, U2.13
ESP_G4: J15.1, U2.4
ESP_G5: J15.2, U2.5
ESP_G6: J15.3, U2.6
ESP_G7: J15.4, U2.7
ESP_G10: J15.9, U2.16
ESP_G11: J15.10, U2.17
ESP_G12: J15.11, U2.18
ESP_G13: J15.12, U2.19
ESP_G14: J16.1, U2.20
ESP_G15: J15.5, U2.8
ESP_G16: J15.6, U2.9
ESP_G21: J16.8, U2.40
ESP_G39: J16.7, U2.31
ESP_G40: J16.6, U2.30
ESP_G41: J16.5, U2.29
ESP_G42: J16.4, U2.28
ESP_G45: J16.9, U2.37
ESP_G46: J15.8, U2.14
ESP_G47: J16.10, U2.39
ESP_G48: J16.11, U2.38
GIMBAL1: J6.2, U1.37
GIMBAL2: J6.3, U1.36
GIMBAL3: J7.2, U1.35
GIMBAL4: J7.3, U1.34
GND: BT1.2, C1.2, C2.2, C3.2, C4.2, C5.2, C7.2, C8.2, C9.2, C10.2, C11.2, D1.2, J1.A1, J1.A12, J1.B1, J1.B12, J2.1, J3.2, J4.2, J5.2, J6.4, J7.4, J8.6, J9.9, J10.9, J11.3, J12.1, J12.MP, J13.1, J14.2, J17.2, R5.2, R6.2, R7.2, R8.2, R16.2, U1.1, U1.26, U1.39, U2.22, U2.23, U2.43, U2.44, U3.1, U4.3, U4.4, U5.2, U7.3, U7.19, U7.20, U7.24, U7.25, U8.1, U9.2
HANDSHAKE_A: U1.8, U2.12
HANDSHAKE_B: U1.17, U2.15
I2C_SCL: J12.4, J13.4, R13.2, U1.32, U7.5
I2C_SDA: J12.3, J13.3, R12.2, U1.33, U7.4
KNOB5: J8.2, U1.31
KNOB6: J8.3, U1.30
KNOB7: J8.4, U1.29
KNOB8: J8.5, U1.28
LATCH_OFF: D4.2, U1.7
LED_CHG_A: D2.1, R10.2
LED_PWR_A: D1.1, R9.2
LINK_RX2: U1.9, U2.11
LINK_TX2: U1.10, U2.10
MID_SENSE: R1.1, U7.9
NEXTION_RX: J2.4, U1.3
NEXTION_TX: J2.5, U1.2
NRF_CE: U1.11, U3.3
NRF_CSN: U1.12, U3.4
OFF_2808: D4.1, U4.6
PMID: C2.1, C3.1, L1.1, U7.21, U7.22
PWRBTN: D3.1, J5.1
REGN: C7.1, R4.1, U7.11
RTC_VBAT: BT1.1, J14.1
SPI_MISO: U1.14, U3.7
SPI_MOSI: U1.13, U3.6
SPI_SCK: U1.38, U3.5
SW1: J9.1, U1.18
SW2: J9.2, U1.19
SW3: J9.3, U1.20
SW4: J9.4, U1.21
SW5: J9.5, U1.22
SW6: J9.6, U1.23
SW7: J9.7, U1.24
SW8: J9.8, U1.48
SW_CHG: C6.2, L1.2, U7.17, U7.18
TRIM1: J10.1, U1.47
TRIM2: J10.2, U1.46
TRIM3: J10.3, U1.45
TRIM4: J10.4, U1.44
TRIM5: J10.5, U1.43
TRIM6: J10.6, U1.42
TRIM7: J10.7, U1.41
TRIM8: J10.8, U1.40
USB_CC1: J1.A5, R7.1
USB_CC2: J1.B5, R8.1
VBAT_RAW: C4.1, C5.1, J3.1, U4.1, U4.2, U7.13, U7.14, U7.15, U7.16
VBAT_SENSE: C11.1, R15.2, R16.1, U1.16
VBAT_SW: R15.1, U4.8, U5.1, U9.1
VBUS_USB: C1.1, J1.A4, J1.A9, J1.B4, J1.B9, R9.1, R10.1, U7.23
WS2812_DATA: R14.1, U1.4
WS2812_OUT: J11.2, R14.2

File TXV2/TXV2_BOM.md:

# TXV2 Revision A — Bill of Materials (shopping list)
*by Claude and Malcolm — July 2026 · quantities are PER BOARD*

## Modules (plug into sockets)
| Qty | Part | Notes |
|---|---|---|
| 1 | **Teensy 4.1** | PJRC — the main MCU |
| 1 | **ESP32-S3-DevKitC-1** (N16R8) | WiFi / BLE sidecar — OTA + phone config |
| 1 | **EBYTE E01-ML01DP5** (nRF24L01+ PA/LNA, SMA) | the RF link module you already use |
| 1 | **Pololu 2808** (PSW03C push-button power switch) | soft power latch |
| 2 | **Pololu 5V buck-boost regulator** (7805 pinout: VIN/GND/VOUT) | one for Nextion, one for everything else |

## Sockets & headers (solder to board)
| Qty | Part | For |
|---|---|---|
| 2 | 24-pin machined/female header strip (2.54mm) | Teensy 4.1 |
| 2 | 22-pin female header strip | ESP32 DevKitC |
| 1 | 2×4 female header | nRF24 module |
| 1 | 7-pin + 1 | 6-pin female strip (or cut from stock) | Pololu 2808 (keyed 6+7) |
| 2 | 3-pin female strip | the two bucks |
| 2 | 1×12 pin header (male, 2.54mm) | ESP spare GPIO A/B |
| 1 | 1×5 pin header (male) | Nextion / FTDI lead (V1 style) |

## Connectors
| Qty | Part | For |
|---|---|---|
| 1 | **AMASS XT30U-F** (female, PCB vertical) | battery |
| 3 | JST-XH 2-pin vertical | BAL · BTN · RTC |
| 1 | JST-XH 3-pin | RGB LED |
| 3 | JST-XH 4-pin | GIMBAL L · GIMBAL R · I2C |
| 1 | JST-XH 6-pin | KNOBS |
| 2 | JST-XH 9-pin | SWITCHES · TRIMS |
| 1 | JST-SH 4-pin (BM04B-SRSS-TB) | QWIIC I2C |
| 1 | **USB-C 16-pin receptacle** (HRO TYPE-C-31-M-12) | charging |
| 1 | CR2032 holder, vertical (Panasonic VS1N style) + CR2032 cell | Teensy clock backup |
| — | matching JST-XH housings + crimp pins for the looms | |

## Charger circuit (hand-solder SMD, back side)
| Qty | Part | Ref |
|---|---|---|
| 1 | **TI BQ25887RGER** (VQFN-24) | U7 — 2-cell charger + balancer |
| 1 | **1µH power inductor, Vishay IHLP-2020** (≥3A) | L1 |
| 1 | AMS1117-3.3 (SOT-223) | U8 — nRF 3.3V rail |

## Diodes & LEDs
| Qty | Part | Ref |
|---|---|---|
| 2 | 1N4001 in SMA package (e.g. M1/S1A) | D3, D4 — soft-power OR |
| 2 | 0805 LED (suggest green + amber) | D1 PWR, D2 CHG |
| 1 | WS2812 RGB LED (panel-mount / breakout with 3-wire lead) | the status light |

## Capacitors
| Qty | Value | Size | Ref |
|---|---|---|---|
| 3 | 10µF 25V | 1206 | C2 C3 C4 (PMID/BAT) |
| 1 | 10µF | 1206 | C9 (RF rail) |
| 1 | 1µF | 0805 | C1 (VBUS) |
| 1 | 4.7µF | 0805 | C7 (REGN) |
| 1 | 47nF | 0805 | C6 (BTST) |
| 1 | 47pF | 0805 | C5 |
| 2 | 100nF | 0805 | C10, C11 |
| 1 | 220µF electrolytic SMD (6.3mm can) | — | C8 (RF bulk) |

## Resistors
| Qty | Value | Size | Ref |
|---|---|---|---|
| 2 | 68R | 1206 | R2 R3 (balance, parallel pair) |
| 2 | 330R | 0805 | R1 (MID), R14 (WS2812 data) |
| 1 | 374R | 0805 | R6 (ILIM) |
| 2 | 470R | 0805 | R9 R10 (LEDs) |
| 1 | 5.11k | 0805 | R4 (TS upper) |
| 1 | 7.5k | 0805 | R5 (TS lower) |
| 2 | 5.1k | 0805 | R7 R8 (USB-C CC) |
| 2 | 4.7k | 0805 | R12 R13 (I2C pullups) |
| 1 | 47k | 0805 | R15 (VBAT divider) |
| 1 | 15k | 0805 | R16 (VBAT divider) |

## Off-board
- RadioMaster 2S 5000mAh pack (male XT30) — you have it
- Nextion NX8048P050 display — from V1
- 16mm vandal momentary button — the power button
- Gimbals / knobs / switches / trims — from the V1 hardware plan
- M3 standoffs ×4 (~5mm) — as V1

## The board itself
**JLCPCB: 4-layer, 1.6mm, 83.3 × 91.7mm, qty 100** — upload `TXV2_MAIN_gerbers.zip`, defaults for everything else.

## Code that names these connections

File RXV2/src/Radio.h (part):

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    // though slot 1's hardware is perfectly fine. The symptom: one
    // radio installed = bind works; add a second physical radio = the
    // CSN floating wrecks slot 1's detection.
    pinMode(PIN_NRF_CSN,  OUTPUT); digitalWrite(PIN_NRF_CSN,  HIGH);
    pinMode(PIN_NRF_CSN2, OUTPUT); digitalWrite(PIN_NRF_CSN2, HIGH);
    pinMode(PIN_NRF_CSN3, OUTPUT); digitalWrite(PIN_NRF_CSN3, HIGH);
    pinMode(PIN_NRF_CE,   OUTPUT); digitalWrite(PIN_NRF_CE,   LOW);
    pinMode(PIN_NRF_CE2,  OUTPUT); digitalWrite(PIN_NRF_CE2,  LOW);
    pinMode(PIN_NRF_CE3,  OUTPUT); digitalWrite(PIN_NRF_CE3,  LOW);

    // Override variant defaults — route MISO off the BOOT-strap pin.
    SPI.begin(PIN_SPI_SCK, PIN_SPI_MISO, PIN_SPI_MOSI, -1);
    delay(50);

    rfTest.beginOk = radio1.begin();
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

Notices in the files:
README.md:
Licence and credits:
Free for other flyers, and derivatives must stay free:
What | Licence
Code: the screen, the receiver, the apps, the web pages, the tools | **GPL-3.0-or-later** ([LICENSE](LICENSE)), with an [app-store exception](LICENSE-EXCEPTION.txt)
The transmitter's Teensy firmware | **GPL-2.0-or-later** ([TXV2/LICENSE](TXV2/LICENSE)), like Version 1
Circuit boards | **CERN-OHL-S-2.0
Manuals, help texts, the screen's pages and sounds, pictures, case files | **CC BY-SA 4.0
Details in [LICENSING.md](LICENSING.md).
Made by Malcolm Messiter**, with **Claude** (Anthropic'
